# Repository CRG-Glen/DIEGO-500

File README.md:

# DIEGO PROJECT

Turn your A500 into an A2000 with this sidecar backplane
CHECKMATE VERSION NOT YET TESTED - DO NOT BUILD

## What's this?  

DIEGO is a Zorro 2 backplane expansion for use on your A500 either as a side car project or within your Checkmate case.  Diego gives you an A2000 compatible CO-PROCESSOR slot (side car version only) along with a full set of 5 ZORRO2 slots all made possible by the onboard Bluster IC.  Bluster is a remake of the classic A2000 Buster chip by LIV2 although it is a custom version for DIEGO to handle inverted clocks and provide some further functions.  

DIEGO has been tested extensively with various CPU and Zorro cards, a list of tested cards is provided below.  If you have anything to add to this list, please get in touch.  

DIEGO is also intended to power your A500 via the passthrough 4 pin connector adjacent to the main 24 pin ATX connector.  Please note that on the Checkmate version has power connected at the side car but also space for a passthrough.  The side car version currently does not have power connected at the side car.  For this version you must use the pass through to power your A500.  

## Ordering

There are currently 3 versions of DIEGO, a side car 5 slot version, a side car 3 slot version and a version for installation within a Checkmate case.  Please note that at present both the 3 slot and checkmate versions have not been tested so build at your own risk.  Checkmate version is currently in testing, I do not recommend building until it's confirmed working and ready.  

Gerber, BOM and CPL files are provided for each in the JLCPCB folder.  

All passives on each version are located on the bottom side (with exception of ferrite bead on checkmate version).  All logic and electrolytic caps are located on the top side.  

Each version of DIEGO is a 4 layer board.  HASL finish is fine for this project, inner layers can be left 0.5oz.  

All signals are routed on the top and bottom layers but there are some power traces on each internal layer along with solid grounds.  

Due to the amount of passives I recommend having your PCB manufacturer fit the bottom side, you then as builder complete the top side.  

While all components are available at JLC several top side parts are getting expensive!  

## Assembly

Assuming you got your boards made with the bottom side completed you may fit out the top side to suit yourself.  I recommend fitting and programming the CPLD first and finish all SMD work before doing the slots as they'll just get in the way!  

NOTE (side car version only): U11 is only required if you're using something in the COPROCESSOR slot that needs a 28mhz clock.  There doesn't seem to be that many (if any) cards that do require this so you may leave this off if you prefer. (this has not been tested as I don't have anything that needs this clock)

FURTHER NOTE: You MUST use LS and ALS logic as per the BOM.  DIEGO was originally built with HCT logic but this caused issues with several boards.  HCT will work if you prefer to use this but you might find some early SCSI cards don't work.  

For the 86pin slot to the A500 on the side car version you will need to bend the pins in to meet the pads on DIEGO.  

For programming the CPLD, the required JED file is available in the CPLD folder or you may get it from LIV2s GitHub.  I use a Raspberry PI to programme CPLDs as per LIV2s guide but use whatever method you're comfortable with.  Just remember if using a PI and if powering 3.3v from the PI, disconnect all other power supplies from DIEGO 500!

## Using your DIEGO

For the most part DIEGO is simply plug and play but there are a few things to keep in mind.
- Firstly there is a single jumper to configure to select which 7mhz clock to use.  If you're using a Rev3 or 5 A500 you must select CPLD clock.  If you're using a Rev6 A500 you can use either but if using A500 clock you need to close JP6 on the A500s motherboard.  If you are using an A500+ you can pick either.  The CPLD clock is derived from _CCK XNOR _CCQK within the CPLD.    
- There is one more pin header labelled CFGIN.  If you have any expansions in your A500 on the autoconfig chain you MUST connect said expansions config out to this config in.  If you don't you'll most likely get a yellow screen or just no zorro cards detected!
- Insert all cards as if this was a real A2000 i.e. the front of DIEGO is the front of an A2000.  Most modern Zorro expansions (especially half length cards) will have an arrow pointing to front or back.  Pay attention to this! If you plug something in wrong expect a dead card and possibly dead Amiga! 
- Zorro 2 cards will autoconfigure themselves just like they would in any Amiga.  To confirm this hold both mouse buttons on start up to access the early start-up menu and select "expansion board diagnostic" (only available to kickstart 2.04 and up)

Side car version only
-  If you're using a true A2000 CPU card in the COPROCESSOR slot (like the N2630) simply insert the card and Bluster will tristate the internal A500 CPU. (this is achieved by Bluster monitoring _BOSS and when asserted, Bluster asserts _BR to the internal CPU)  
- If you are using an A500 type accelerator in the COPROCESSOR slot such as TF536 or a PISTORM (including PISTORM 2000), you MUST open the A500 and remove the internal CPU.  Even if you manually assert _BOSS, the E clocks will clash and it won't work.  There is NO fix for this!  A2000 accelerators work as they monitor E and sync to it or generate it as necessary.  

Checkmate version only
- If you're using an accelerator in the A500s CPU socket you may need to connect its config out to the config in pin on DIEGO.  If you get a yellow screen or crash on boot this is the likely cause.  

## Testing and Results

With thanks to GADGETUK, SPARX, CATHERS and ANDI@HBR we've been able to test and confirm that most boards 
work fine in DIEGO.  The below table lists those boards tested and confirmed as working or not.

| Card Type | Name | Status |
|---|---|---|
| SCSI | Commodore A2090A | Working but very fussy (requires LS and ALS logic).  Only bluescsi V2 and only in raw mode. |
| SCSI | Commodore A2091 | Working |
| SCSI | GVP Series II HC+8 | Working |
| IDE |	Ripple IDE | Working |
| IDE |	AT-Bus clone | Working |
| IDE |	Buddha | Working |
| RAM |	Amigakit ZORRAM | Working |
| RAM |	Gottagofastram 2000 | Working |
| Sound | Prelude | Working |
| Sound | Toccata | Working |
| Sound | AD516 audio card | Working |
| RTG |	GBAPII | Working |
| RTG |	Merlin | Working |
| Networking |	Hydranet | Working |
| IO | BSC Multiface 3 | Working |
| IO | Thylacine USB (old longer model) | Working |
| Multi-feature | LAN-IDE-Clock | Working/Working/Not tested |
| CPU |	A2630 | Working |
| CPU |	N2630 | Working |
| CPU |	TF520 | Working |
| CPU |	TF536 | Working |
| CPU |	TK2 | Working |
| CPU |	Pistorm | Working |
| CPU |	Pistorm 2k | Working |
| Bridgeboard |	Commodore A2286 | Working |
| Bridgeboard |	Commodore A2086 | Working |

If you can add to this table please get in touch!

## Case

At present there is no full case but there is a base that will hold either the 3 or 5 slot version of Diego level with the side car slot of your A500.  I'm not great at designing these things so if you want to help please get in touch.  STL files are in the BASE folder.  

With thanks to Maikiro on Discord we now had a proper base for the 5 slot version.  He has kindly created 3 version of this to suit positioning of your ATX power connector.  STLs for these are provided in the BASE/Maikiro folder.

## FAQ

Several people have asked about adding ISA slots, a video slot or making this remote with a ribbon cable to the A500.  

ISA slots - DIEGO side car has been designed so that you could in theory add ISA slots on a separate board, the Zorro slots 
in relation to the edge of the PCB are positioned to allow this.  I haven't designed an ISA slot extension as I don't have a bridge board to test it with.  
The Checkmate version could be redesigned to incorporate ISA slots although you will loose 2 of the half length zorro slots.  For this release it was thought more useful to include 5 zorro slots. 

Video slot - There are no plans to add a video slot.  Very few of the required signals are on the A500s side car so it would need a multicore ribbon from DENISE.  

Ribbon Cable for remote use - If you want to try a ribbon cable to have DIEGO remote from your 500 you can simply solder one onto the edge connector but I don't expect this to work without further buffering! (like in the bodega bay).

A1000 version - This is coming along with a rework of the entire project to sit vertical beside your 500.  It'll take a while to figure out so please bear with me.  

## License

This project represents countless hours of work by not just me but LIV2 and everyone involved in testing.  It is however released under a CERN Open Hardware Licence v2 for the community to enjoy.  

While I cannot put any direct stipulations into this I would ask that it should only be built and sold at cost plus time.  

If you plan on forking or using this as the basis for any other works you must comply with the following as per the terms of the license attributed to this project.
1. All attributions and credits as presented within this github and on the DIEGO 500 PCB must be maintained and carried through.
2. Any derivative of this project must be also be released open source.

If you are doing a build of these please consider a £1 donation per board to my kofi - https://ko-fi.com/crg_glen.  I'm at least £500 into this project so any support to recoup this is appreicated.  

## Credits

Based on A2000 rev6 schematics by Dave Haynie and EATX2000 by Jasonsbeer

PCB by CRG(Glen)

Bluster by LIV2

Artwork by Brick Studios

Testing by GadgetUK, Sparx, Cathers and Andi@HBR

Thanks to Mikerochip for inspiration for the PSU switch, Neil from Retro4U for loaning his GVP for testing and Kazanoz for helping with the BOM

Special thanks to GadgetUK for hosting the test room on his discord and LIV2 for his work modifying Bluster

Extra Special thanks to Rob Cranley and Steve Jones for their help on the Checkmate version

Why is it called Diego?  Well... this project started solely as a Zorro 2 expansion and to implement that I first had
to understand how the Zorro bus worked.  You might say I had to unmask Zorro.  The character of Zorro unmasked is called Don Diego so Diego 500 or Diego Checkmate.

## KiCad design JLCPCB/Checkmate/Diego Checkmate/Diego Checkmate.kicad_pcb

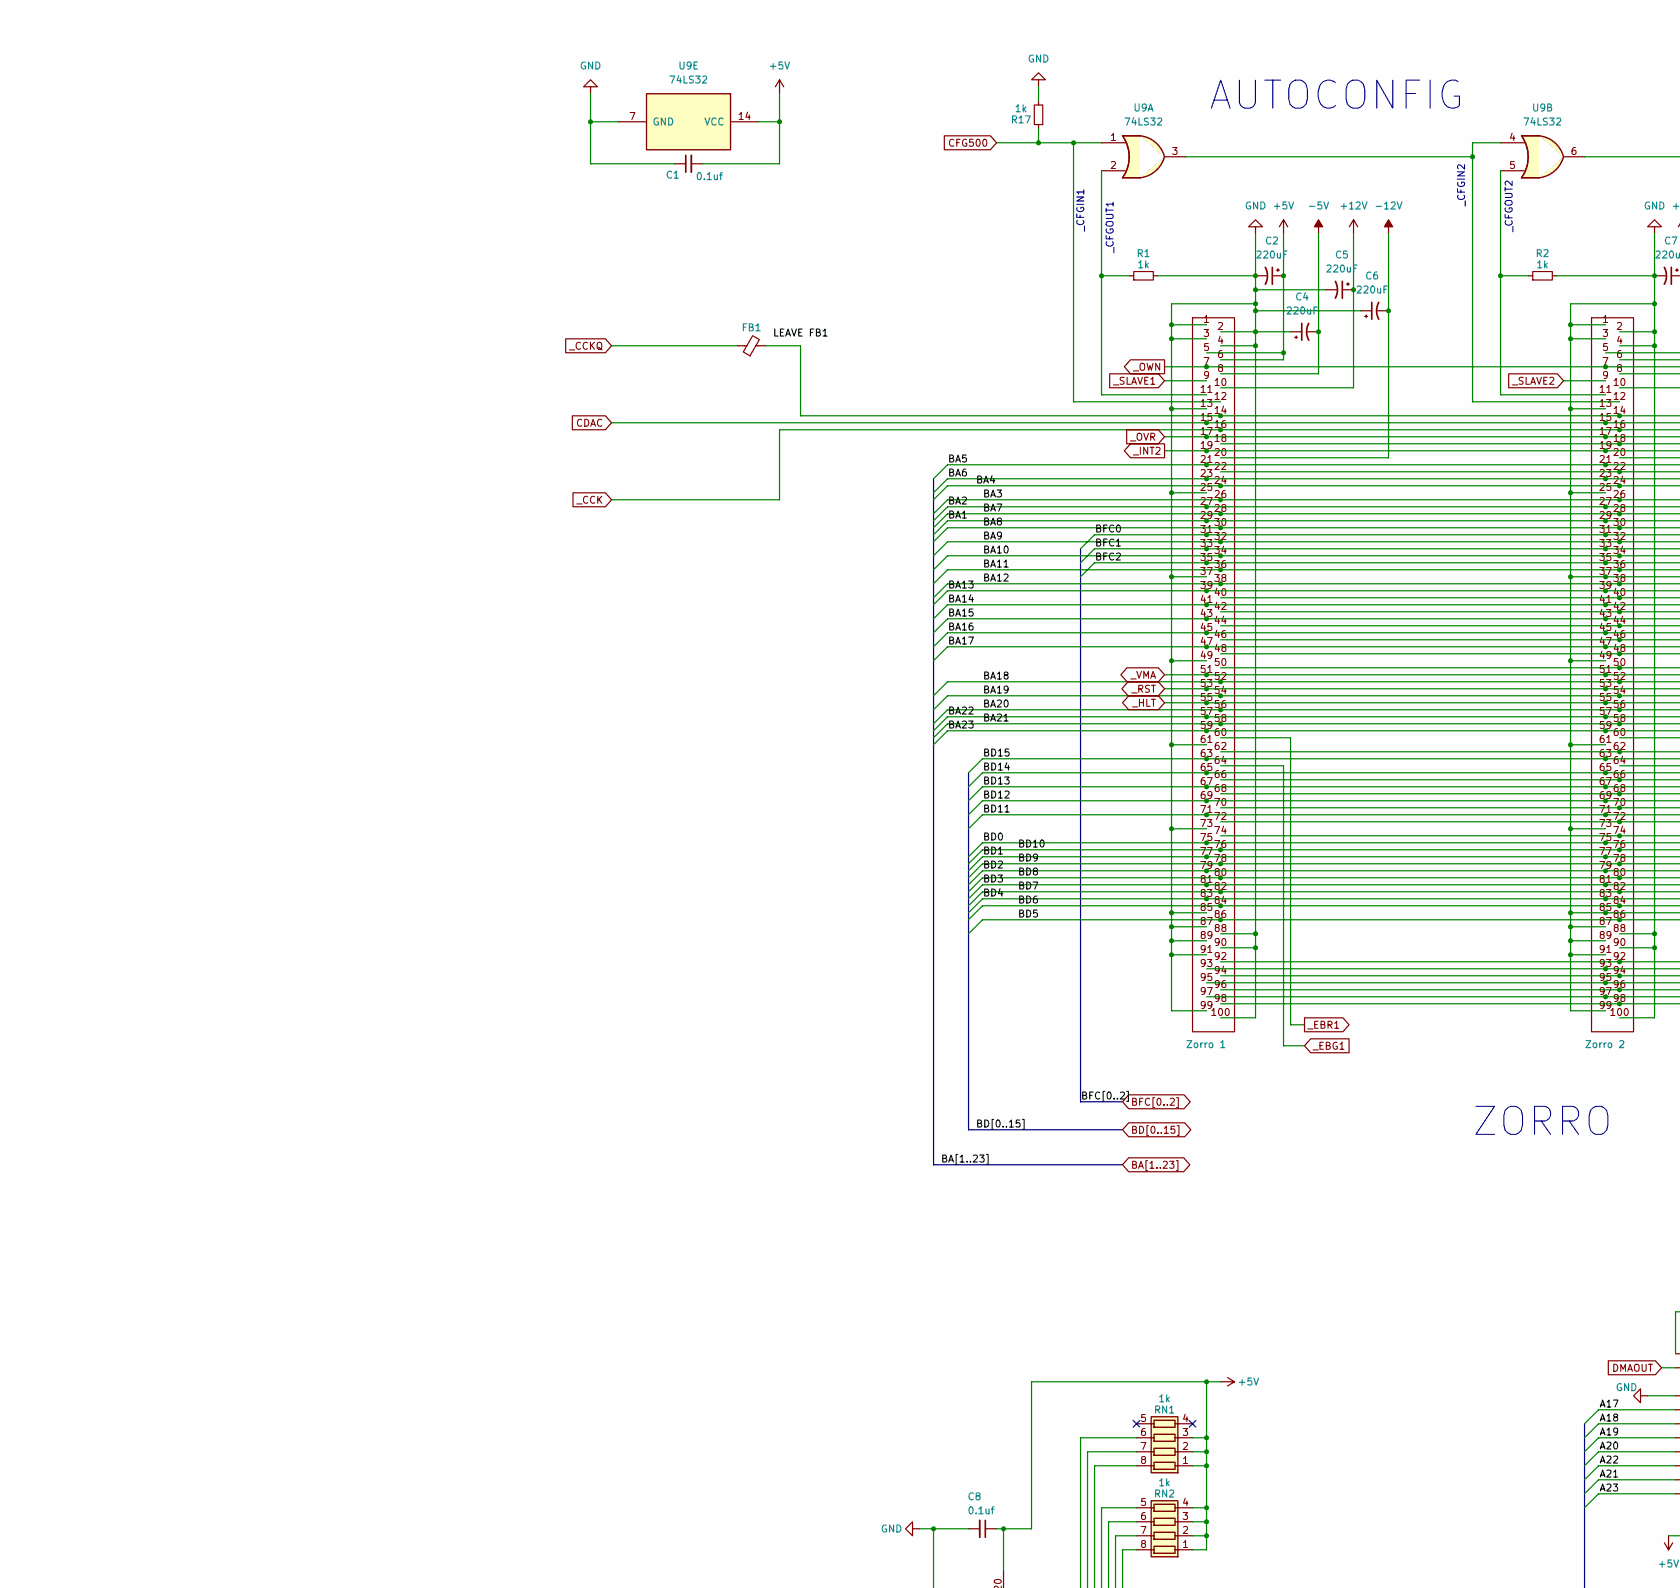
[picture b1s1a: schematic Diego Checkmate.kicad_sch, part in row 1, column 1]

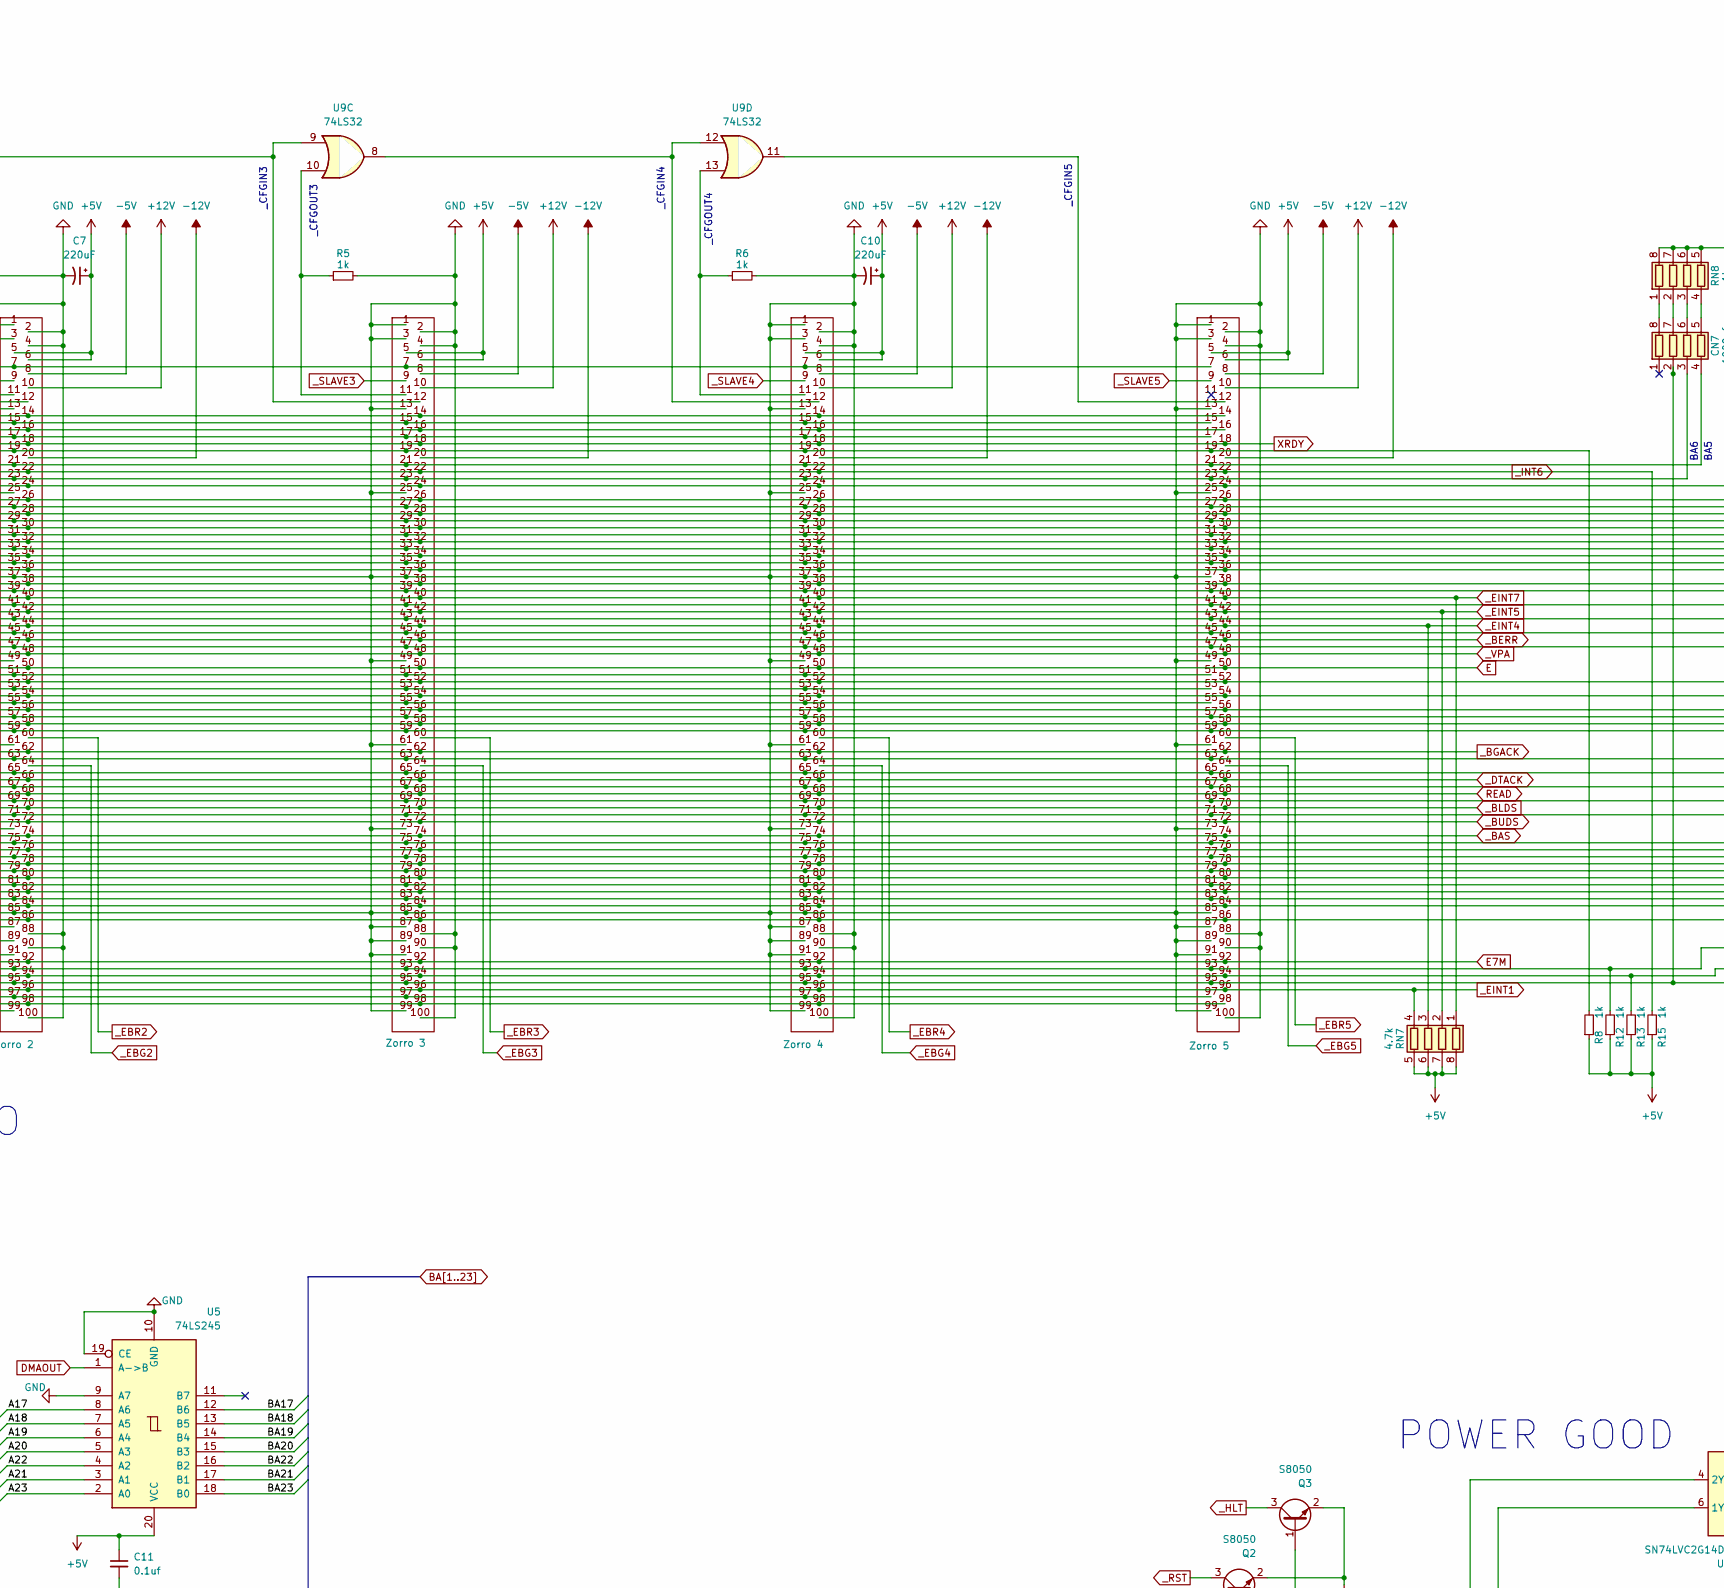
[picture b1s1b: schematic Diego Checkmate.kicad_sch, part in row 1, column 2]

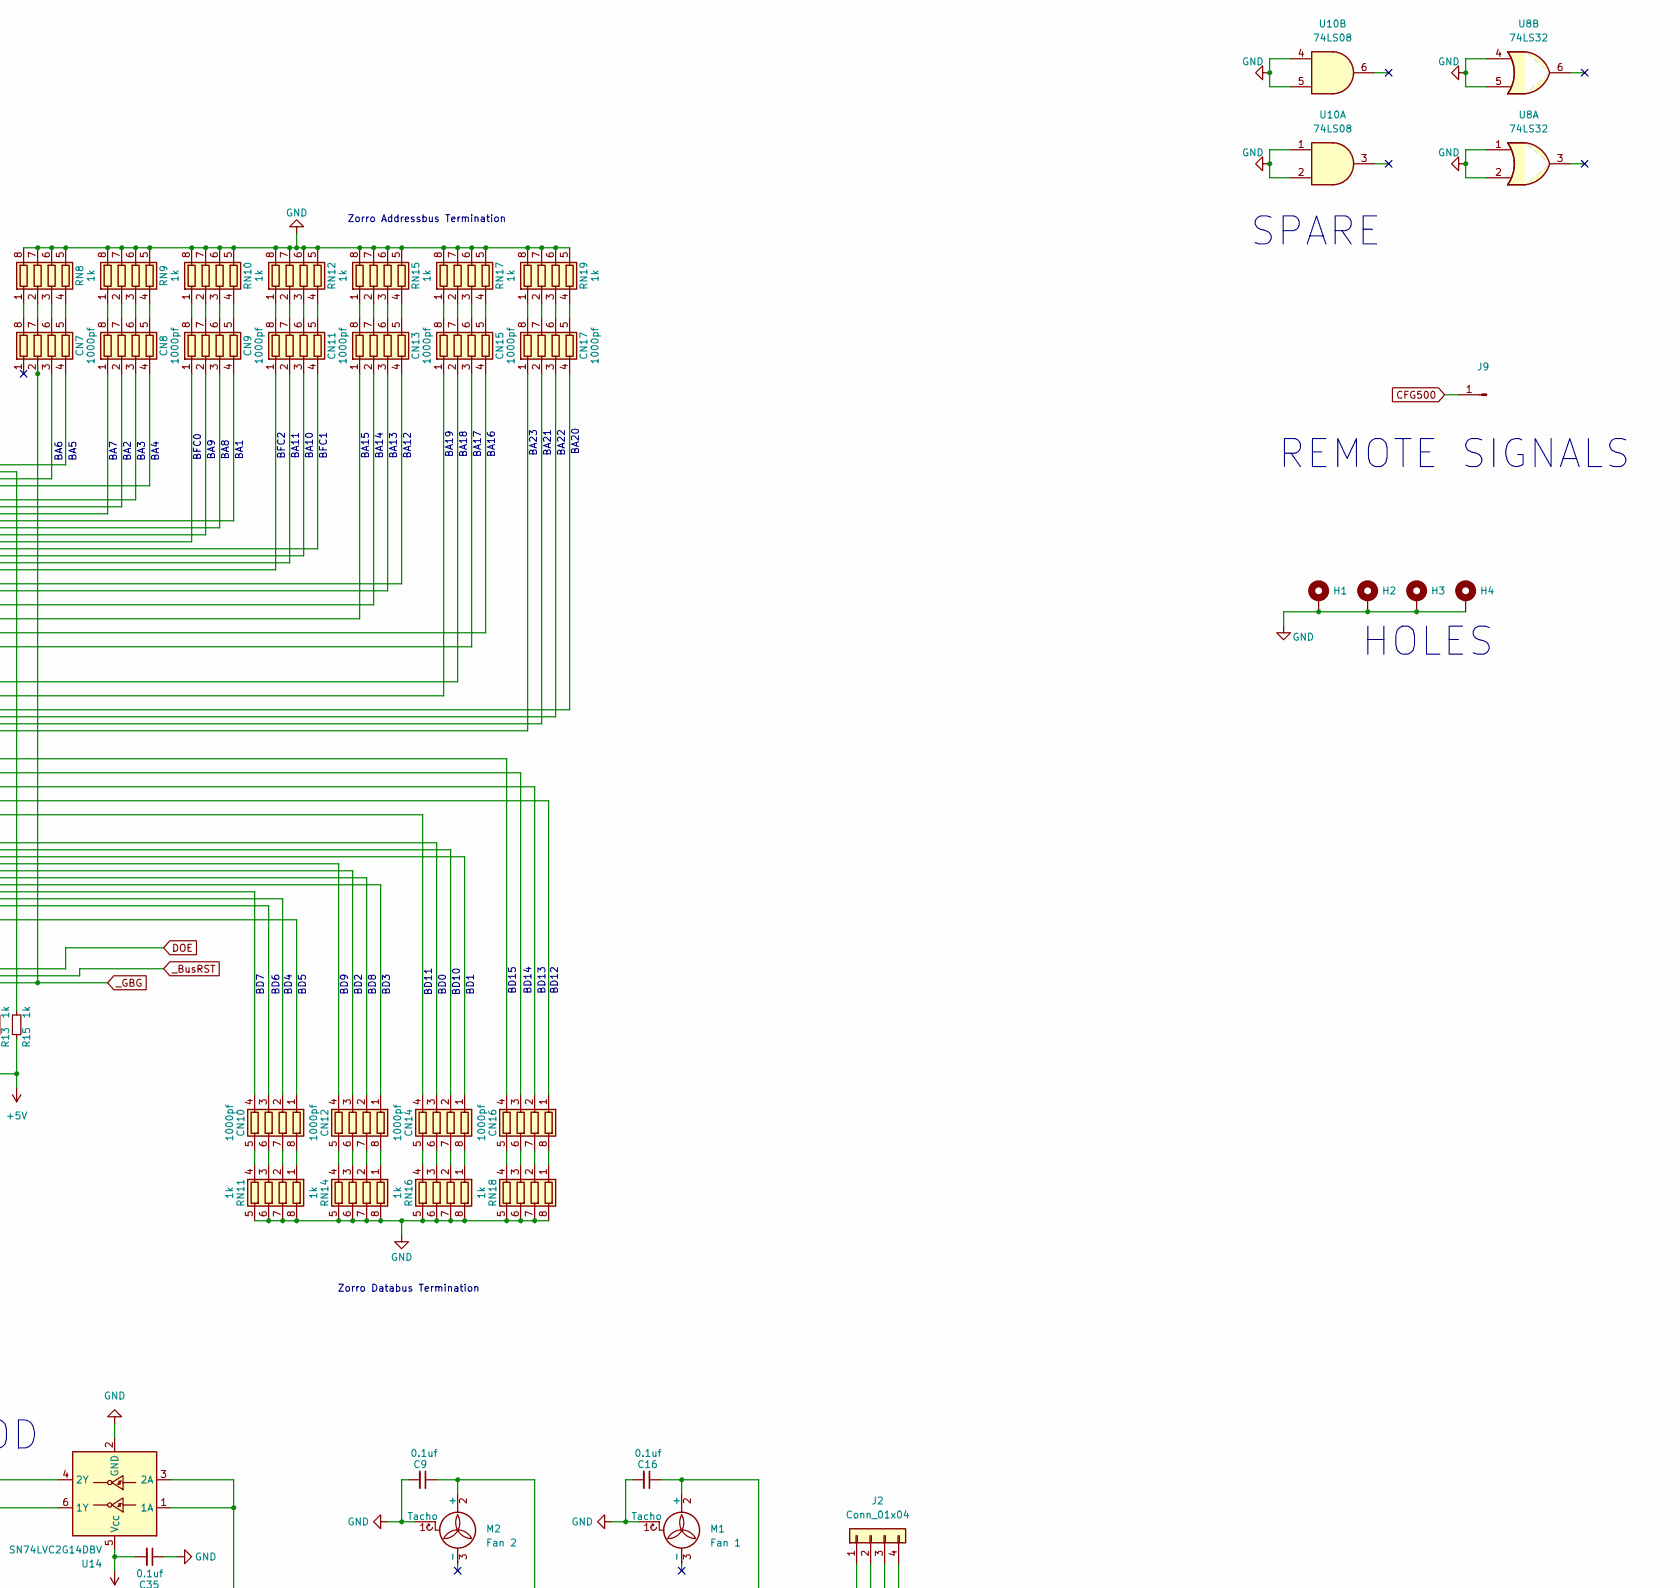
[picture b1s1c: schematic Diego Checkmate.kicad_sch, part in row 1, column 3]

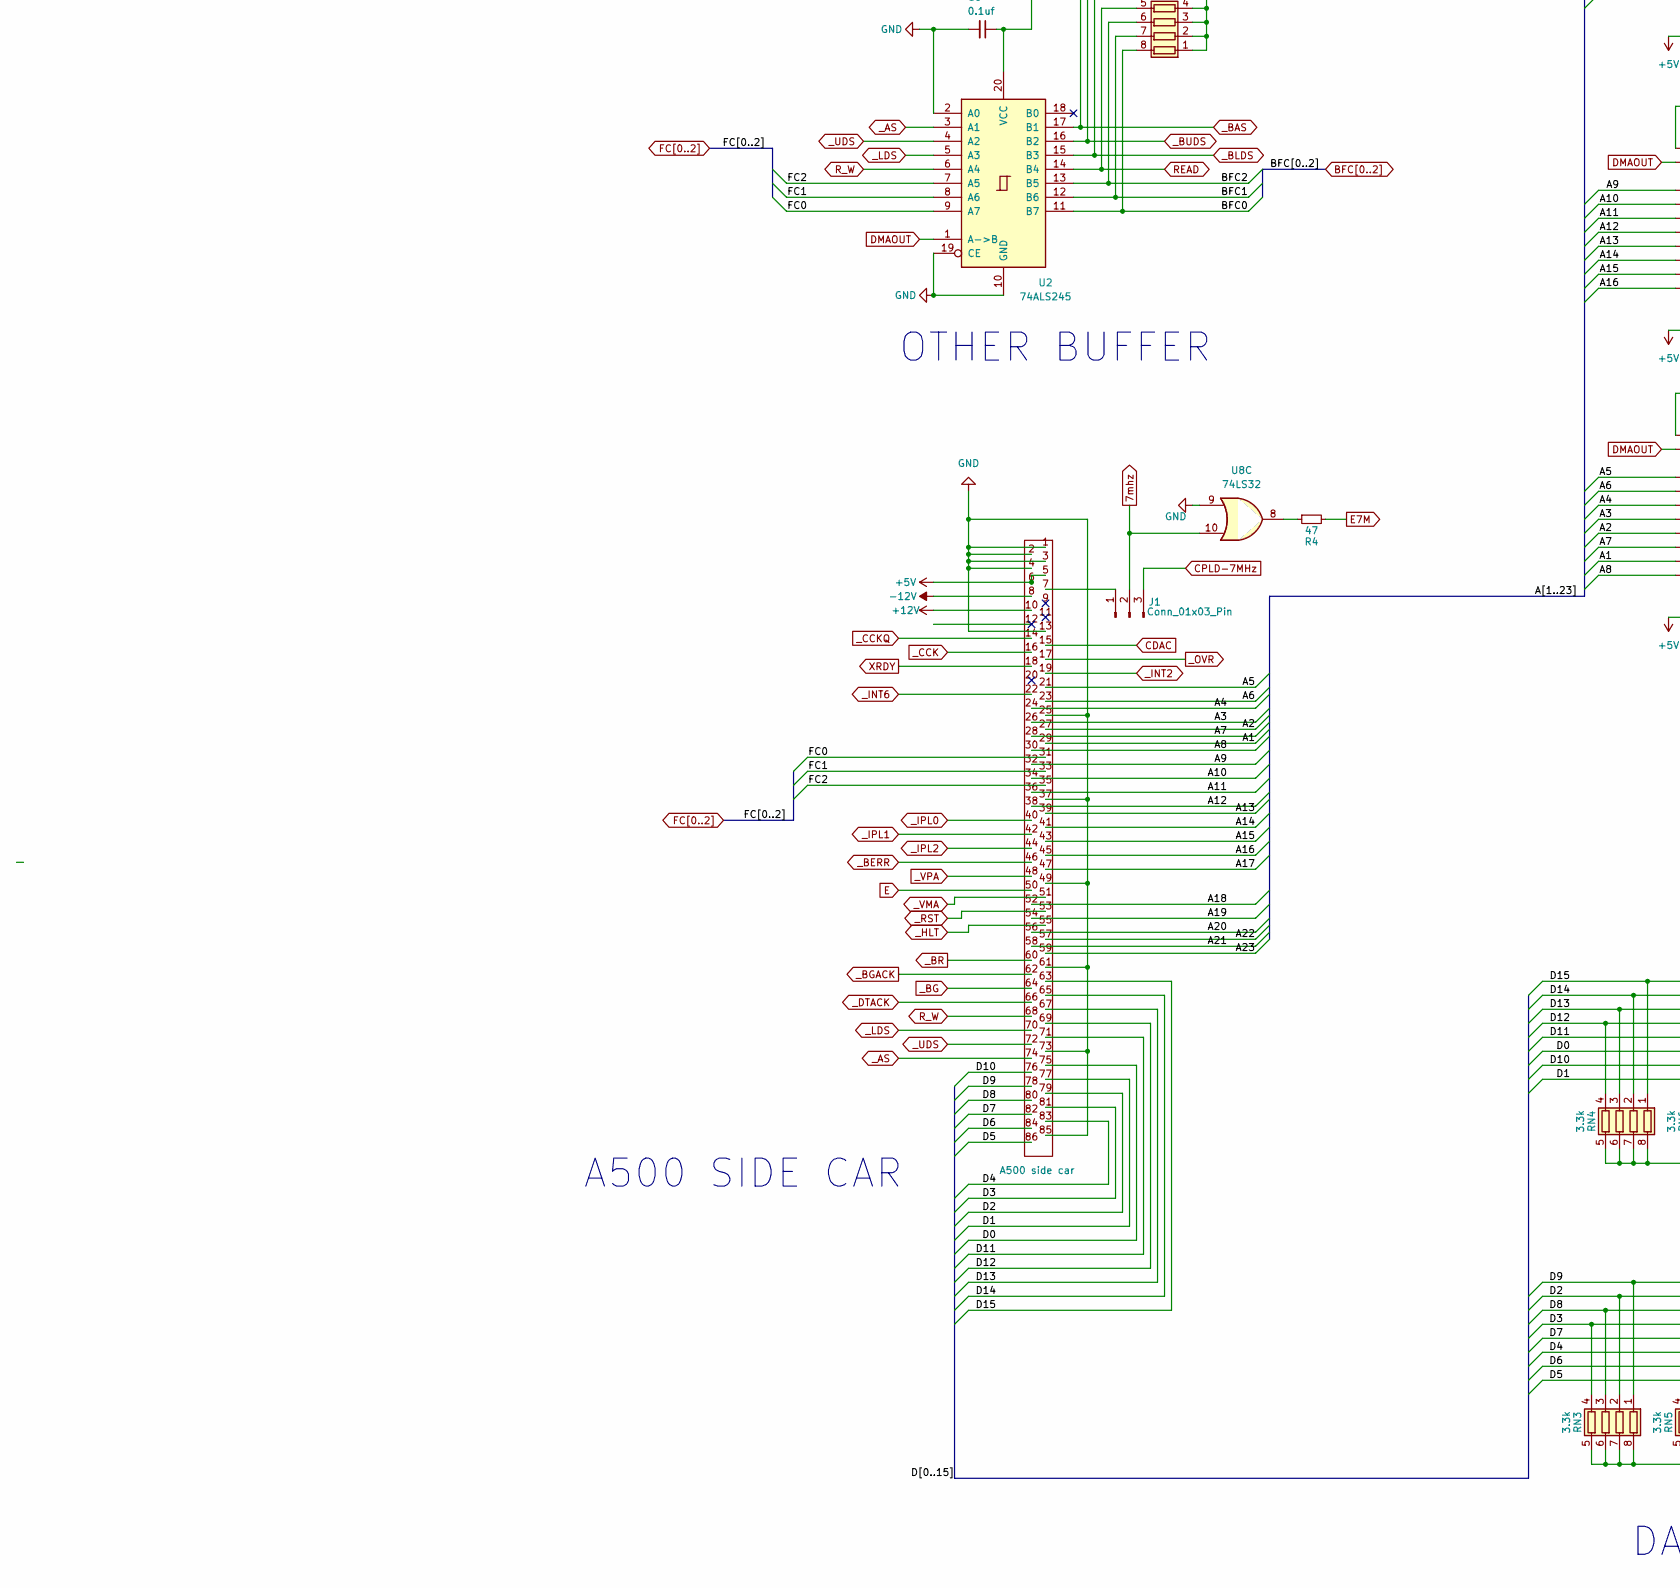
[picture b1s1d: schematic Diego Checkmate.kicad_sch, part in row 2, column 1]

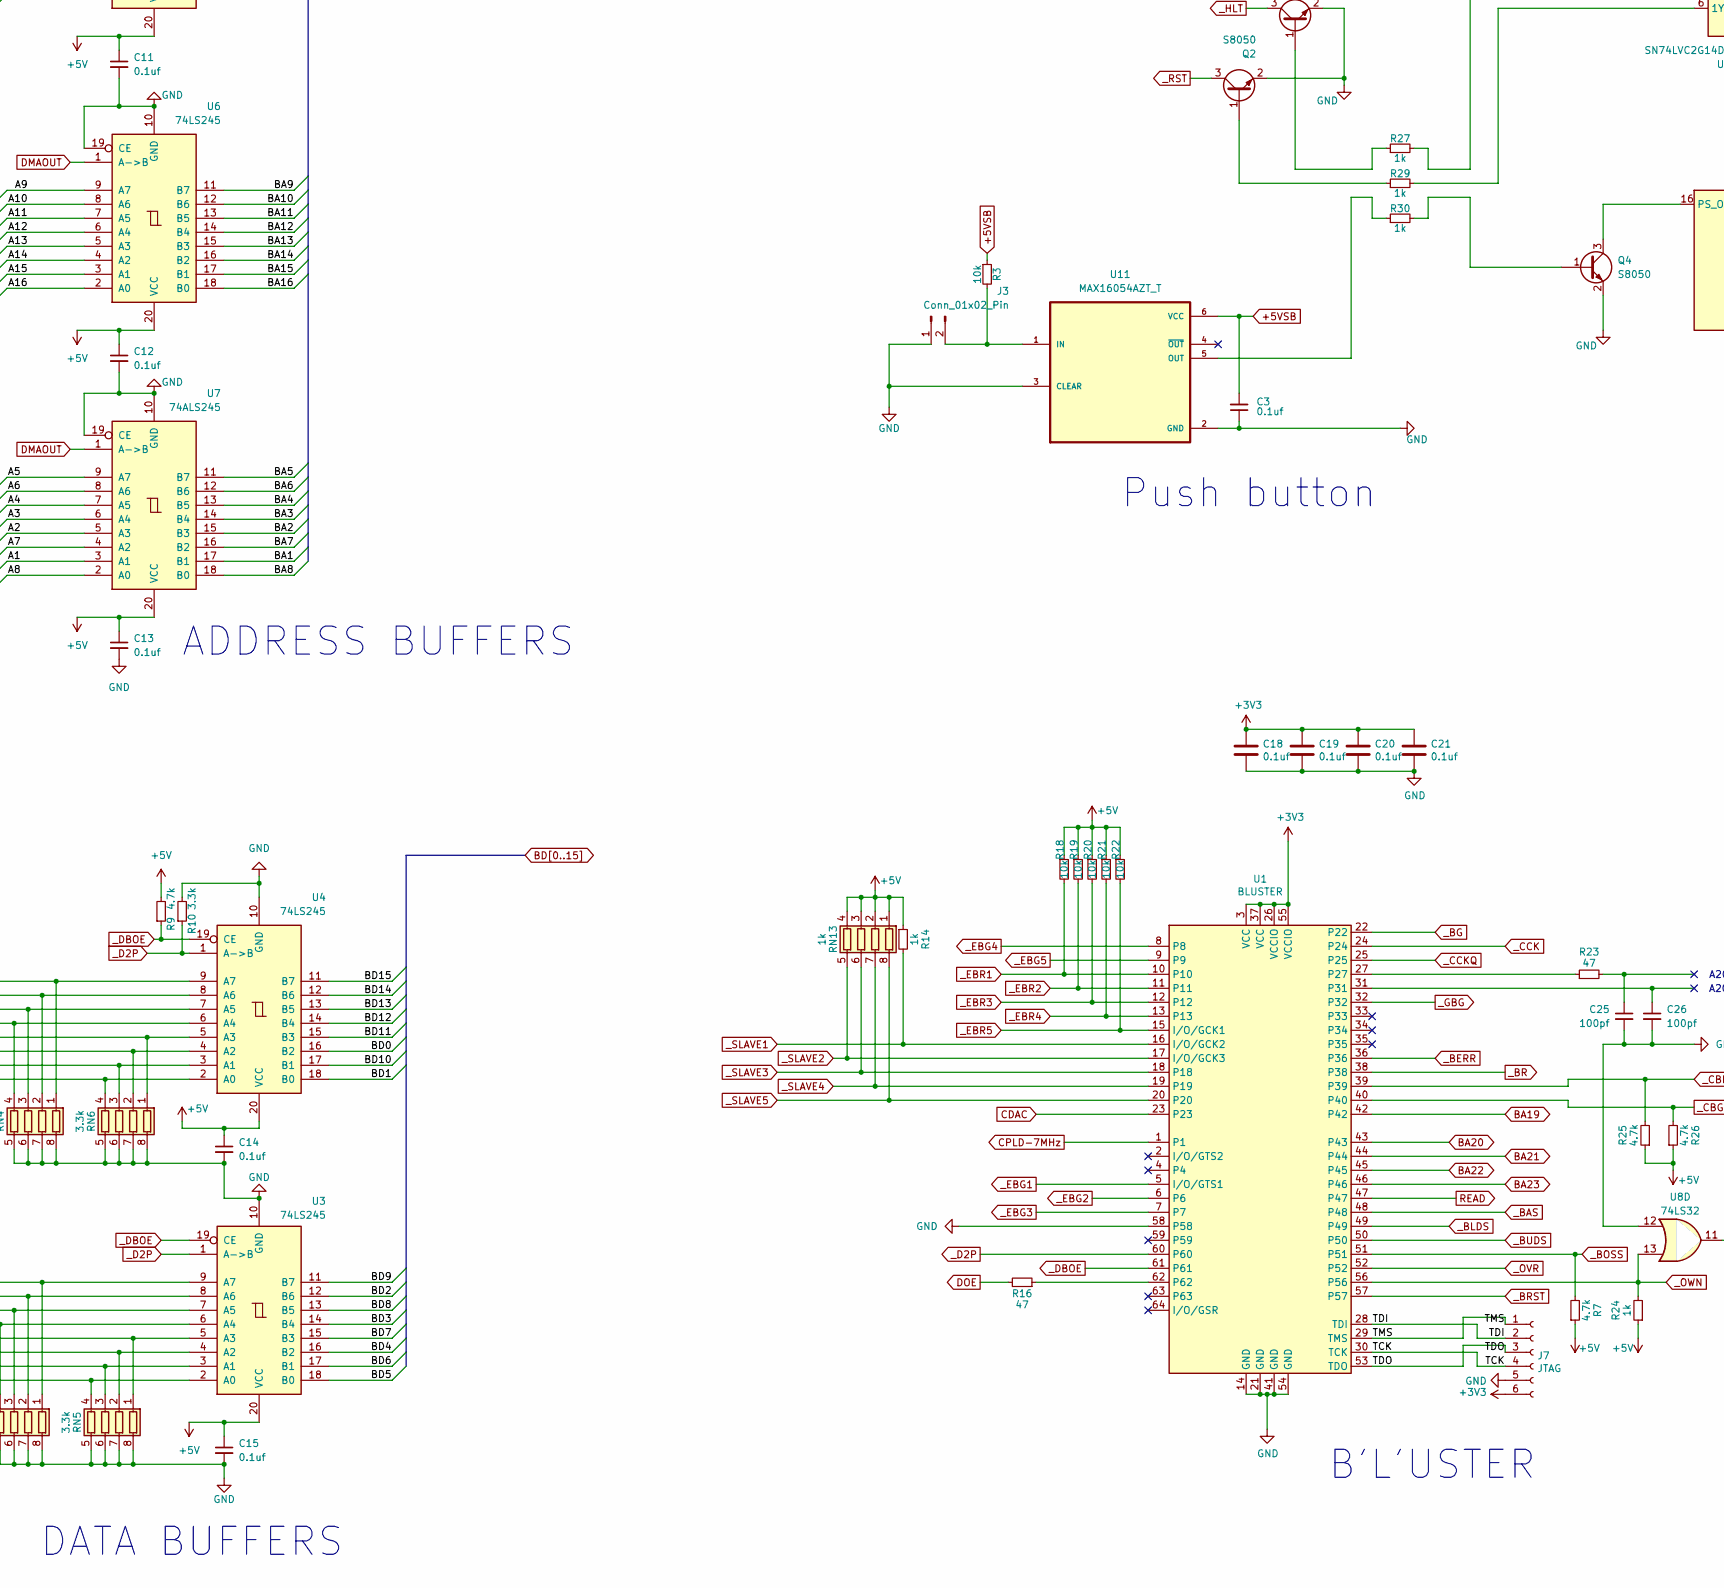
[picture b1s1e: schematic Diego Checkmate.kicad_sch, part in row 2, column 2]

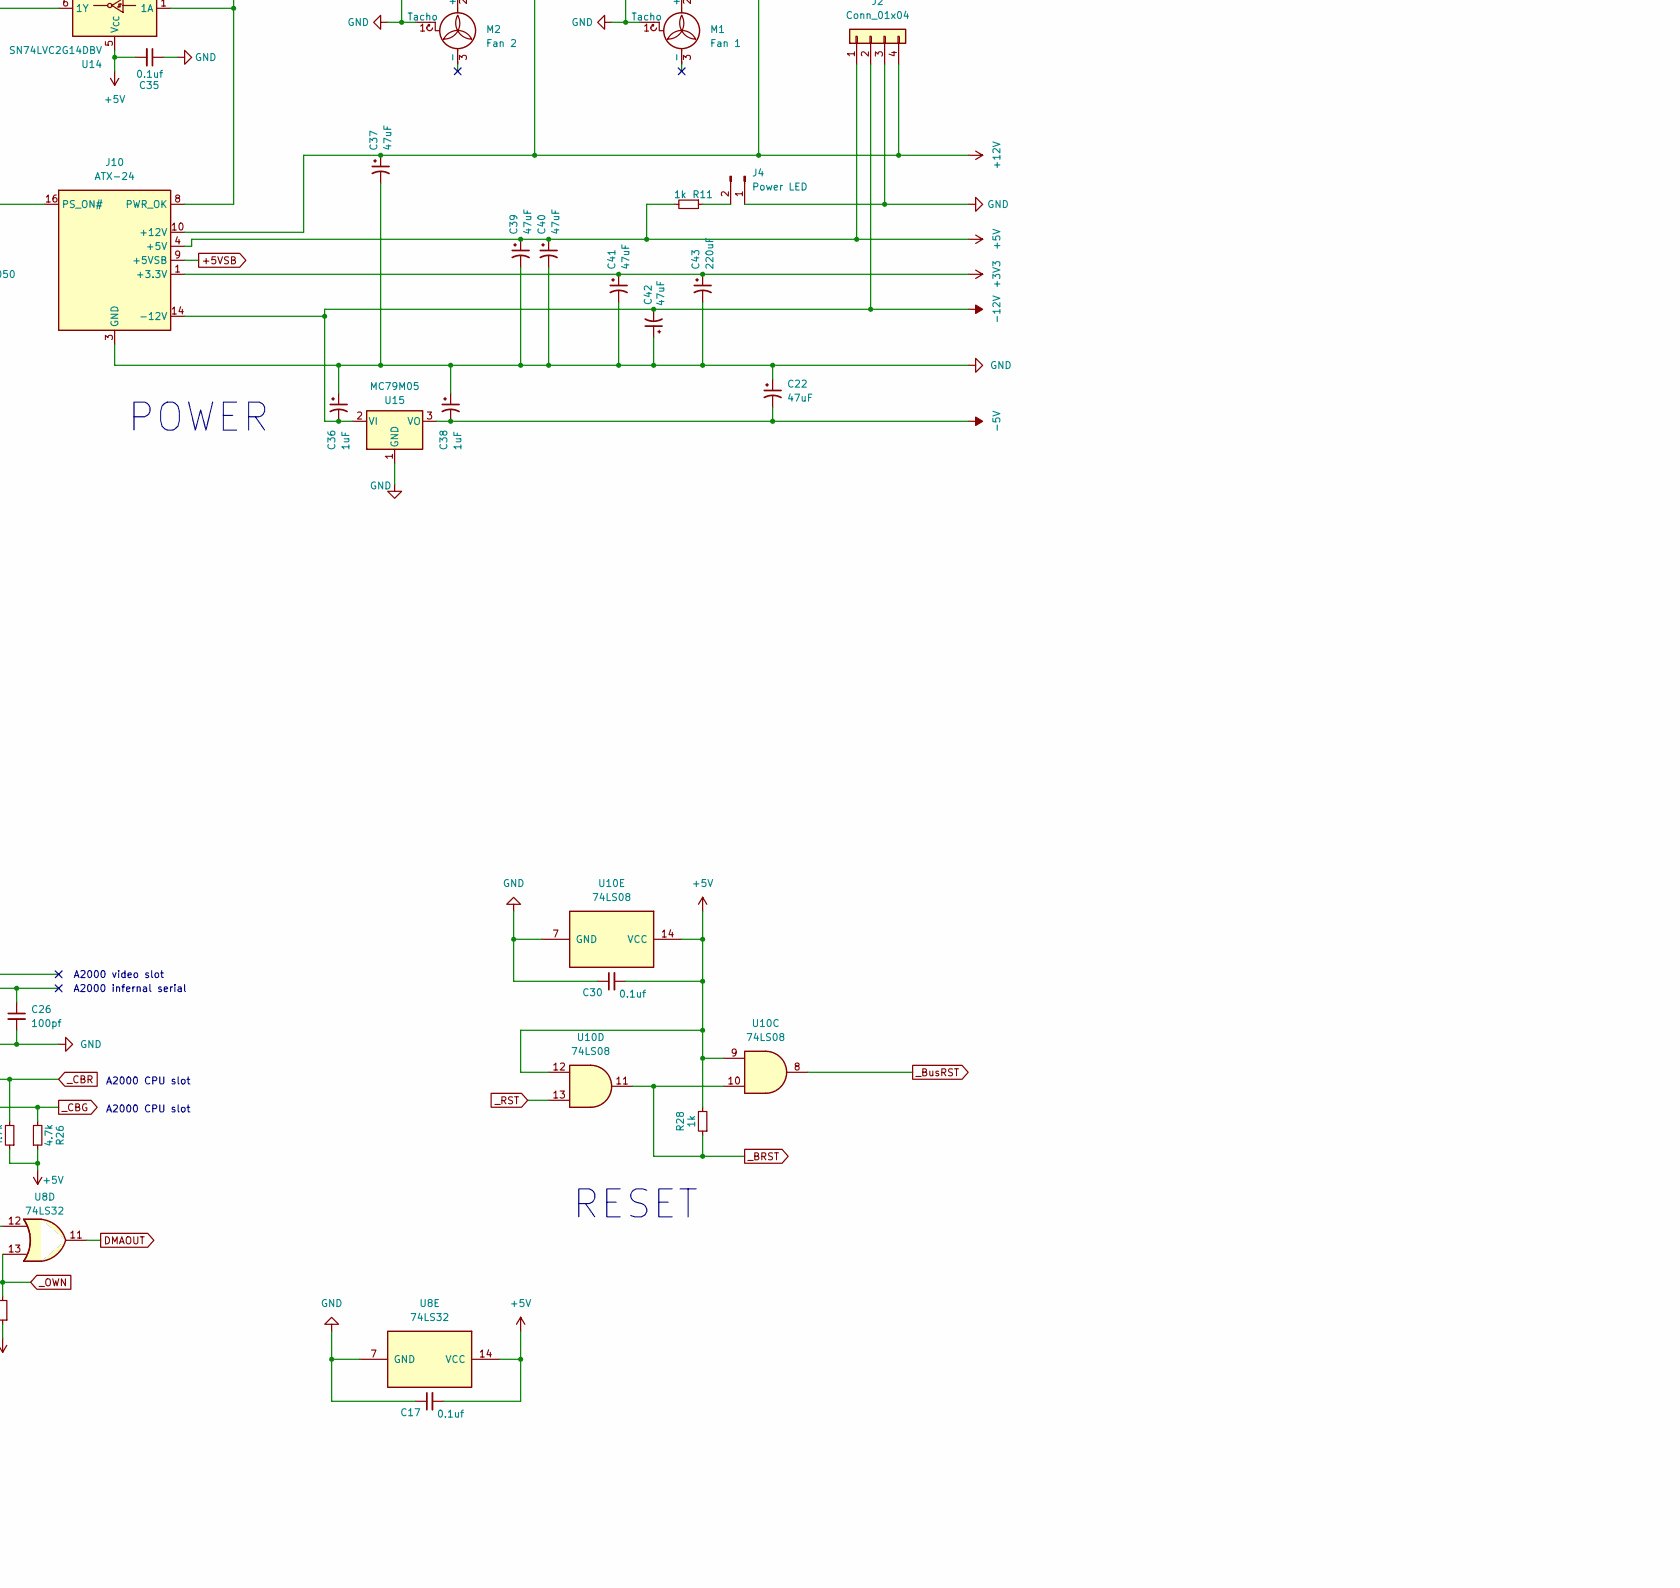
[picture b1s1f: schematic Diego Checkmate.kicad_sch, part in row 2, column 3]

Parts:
C1, C3, C8, C9, C11, C12, C13, C14, C15, C16, C17, C30, C35: 0.1uf; C_0805_2012Metric; LCSC C49678
C2, C4, C5, C6, C7, C10, C43: 220uF; CP_Elec_6.3x7.7; LCSC C278407
C18, C19, C20, C21: 0.1uf; C_0805_2012Metric_Pad1.18x1.45mm_HandSolder; LCSC C49678
C22, C37, C39, C40, C41, C42: 47uF; CP_Elec_6.3x7.7; LCSC C336249
C25, C26: 100pf; C_0805_2012Metric; LCSC C1790
C36, C38: 1uF; CP_Elec_4x5.4; LCSC C3348
CN1: A500 side car; Samtec_HLE-150-02-xx-DV-TE_2x43_P2.54mm_Horizontal; LCSC C5173317
CN2: Zorro 1; Samtec_HLE-150-02-xx-DV-TE_2x50_P2.54mm_Horizontal; LCSC C5173320
CN3: Zorro 2; Samtec_HLE-150-02-xx-DV-TE_2x50_P2.54mm_Horizontal; LCSC C5173320
CN4: Zorro 3; Samtec_HLE-150-02-xx-DV-TE_2x50_P2.54mm_Horizontal; LCSC C5173320
CN5: Zorro 4; Samtec_HLE-150-02-xx-DV-TE_2x50_P2.54mm_Horizontal; LCSC C5173320
CN6: Zorro 5; Samtec_HLE-150-02-xx-DV-TE_2x50_P2.54mm_Horizontal; LCSC C5173320
CN7, CN8, CN9, CN10, CN11, CN12, CN13, CN14, CN15, CN16, CN17: 1000pf; R_Array_Convex_4x0603; LCSC C541606
FB1: FerriteBead_Small; D_0805_2012Metric; LCSC C1015
H1, H2, H3, H4: MountingHole_Pad; MountingHole_4.3mm_M4_DIN965_Pad_TopBottom
J1: Conn_01x03_Pin; PinHeader_1x03_P2.54mm_Vertical
J2: Conn_01x04; Molex_KK-396_A-41791-0004_1x04_P3.96mm_Vertical
J3: Conn_01x02_Pin; PinHeader_1x02_P2.54mm_Vertical
J4: Power LED; PinHeader_1x02_P2.54mm_Vertical
J7: JTAG; PinHeader_1x06_P2.54mm_Vertical
J9: Conn_01x01_Pin; PinHeader_1x01_P2.54mm_Vertical
J10: ATX-24; Molex_Mini-Fit_Jr_5566-24A_2x12_P4.20mm_Vertical
M1: Fan 1; FanPinHeader_1x03_P2.54mm_Vertical
M2: Fan 2; FanPinHeader_1x03_P2.54mm_Vertical
Q2, Q3, Q4: S8050; SOT-23; LCSC C2146
R1, R2, R5, R6, R8, R11, R12, R13, R14, R15, R17, R24, R27, R28, R29, R30: 1k; R_0805_2012Metric; LCSC C17513
R3, R18, R19, R20, R21, R22: 10k; R_0805_2012Metric; LCSC C17414
R4, R16, R23: 47; R_0805_2012Metric; LCSC C17714
R7, R9, R25, R26: 4.7k; R_0805_2012Metric; LCSC C17673
R10: 3.3k; R_0805_2012Metric; LCSC C26010
RN1, RN2, RN8, RN9, RN10, RN11, RN12, RN13, RN14, RN15, RN16, RN17, RN18, RN19: 1k; R_Array_Convex_4x0603; LCSC C20197
RN3, RN4, RN5, RN6: 3.3k; R_Array_Convex_4x0603; LCSC C425215
RN7: 4.7k; R_Array_Convex_4x0603; LCSC C66697
U1: BLUSTER; TQFP-64_10x10mm_P0.5mm; LCSC C90569
U2, U7: 74ALS245; SO-20_5.3x12.6mm_P1.27mm; LCSC C2675885
U3, U4, U5, U6: 74LS245; SO-20_5.3x12.6mm_P1.27mm; LCSC C7753
U8, U9: 74LS32; SO-14_3.9x8.65mm_P1.27mm; LCSC C116812
U10: 74LS08; SO-14_3.9x8.65mm_P1.27mm; LCSC C6802
U11: MAX16054AZT_T; SOT-23-6; LCSC C79401
U14: SN74LVC2G14DBV; SOT-23-6; LCSC C12401
U15: MC79M05; TO-252-2; LCSC C126401

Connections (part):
7mhz: J1.2, U8.10
+3V3: C18.1, C19.1, C20.1, C21.1, C41.1, C43.1, J7.6, J10.1 (+3.3V), J10.2 (+3.3V), J10.12 (+3.3V), J10.13 (+3.3V), U1.3 (VCC), U1.26 (VCCIO), U1.37 (VCC), U1.55 (VCCIO)
+5V: C1.2, C2.1, C7.1, C8.1, C10.1, C11.1, C12.1, C13.1, C14.1, C15.1, C17.2, C30.2, C35.2, C39.1, C40.1, CN1.5, CN1.6, CN2.5, CN2.6, CN3.5, CN3.6, CN4.5, CN4.6, CN5.5, CN5.6, CN6.5, CN6.6, J2.1, J10.4 (+5V), J10.6 (+5V), J10.21 (+5V), J10.22 (+5V), J10.23 (+5V), R7.1, R8.1, R9.2, R11.2, R12.1, R13.1, R14.1, R15.1, R18.1, R19.1, R20.1, R21.1, R22.1, R24.1, R25.1, R26.1, R28.2, RN1.1 (R1.1), RN1.2 (R2.1), RN1.3 (R3.1), RN2.1 (R1.1), RN2.2 (R2.1), RN2.3 (R3.1), RN2.4 (R4.1), RN7.5 (R4.2), RN7.6 (R3.2), RN7.7 (R2.2), RN7.8 (R1.2), RN13.1 (R1.1), RN13.2 (R2.1), RN13.3 (R3.1), RN13.4 (R4.1), U2.20 (VCC), U3.20 (VCC), U4.20 (VCC), U5.20 (VCC), U6.20 (VCC), U7.20 (VCC), U8.14 (VCC), U9.14 (VCC), U10.9, U10.12, U10.14 (VCC), U14.5 (V_{CC})
+5VSB: C3.2, J10.9 (+5VSB), R3.1, U11.6 (VCC)
+12V: C5.1, C9.1, C16.1, C37.1, CN1.10, CN2.10, CN3.10, CN4.10, CN5.10, CN6.10, J2.4, J10.10 (+12V), J10.11 (+12V), M1.2 (+), M2.2 (+)
-5V: C4.2, C22.2, C38.2, CN2.8, CN3.8, CN4.8, CN5.8, CN6.8, U15.3 (VO)
-12V: C6.2, C36.2, C42.2, CN1.8, CN2.20, CN3.20, CN4.20, CN5.20, CN6.20, J2.2, J10.14 (-12V), U15.2 (VI)
/A1: CN1.29, U7.3 (A1)
/A2: CN1.27, U7.5 (A3)
/A3: CN1.26, U7.6 (A4)
/A4: CN1.24, U7.7 (A5)
/A5: CN1.21, U7.9 (A7)
/A6: CN1.23, U7.8 (A6)
/A7: CN1.28, U7.4 (A2)
/A8: CN1.30, U7.2 (A0)
/A9: CN1.32, U6.9 (A7)
/A10: CN1.34, U6.8 (A6)
/A11: CN1.36, U6.7 (A5)
/A12: CN1.38, U6.6 (A4)
/A13: CN1.39, U6.5 (A3)
/A14: CN1.41, U6.4 (A2)
/A15: CN1.43, U6.3 (A1)
/A16: CN1.45, U6.2 (A0)
/A17: CN1.47, U5.8 (A6)
/A18: CN1.52, U5.7 (A5)
/A19: CN1.54, U5.6 (A4)
/A20: CN1.56, U5.5 (A3)
/A21: CN1.58, U5.3 (A1)
/A22: CN1.57, U5.4 (A2)
/A23: CN1.59, U5.2 (A0)
/D0: CN1.75, RN6.2 (R2.1), U4.4 (A2)
/D1: CN1.77, RN6.4 (R4.1), U4.2 (A0)
/D2: CN1.79, RN3.2 (R2.1), U3.8 (A6)
/D3: CN1.81, RN3.4 (R4.1), U3.6 (A4)
/D4: CN1.83, RN5.2 (R2.1), U3.4 (A2)
/D5: CN1.86, RN5.4 (R4.1), U3.2 (A0)
/D6: CN1.84, RN5.3 (R3.1), U3.3 (A1)
/D7: CN1.82, RN5.1 (R1.1), U3.5 (A3)
/D8: CN1.80, RN3.3 (R3.1), U3.7 (A5)
/D9: CN1.78, RN3.1 (R1.1), U3.9 (A7)
/D10: CN1.76, RN6.3 (R3.1), U4.3 (A1)
/D11: CN1.71, RN6.1 (R1.1), U4.5 (A3)
/D12: CN1.69, RN4.4 (R4.1), U4.6 (A4)
/D13: CN1.67, RN4.3 (R3.1), U4.7 (A5)
/D14: CN1.65, RN4.2 (R2.1), U4.8 (A6)
/D15: CN1.63, RN4.1 (R1.1), U4.9 (A7)
/TCK: J7.4, U1.30 (TCK)
/TDI: J7.2, U1.28 (TDI)
/TDO: J7.3, U1.53 (TDO)
/TMS: J7.1, U1.29 (TMS)
BA1: CN2.29, CN3.29, CN4.29, CN5.29, CN6.29, CN9.4 (R4.1), U7.17 (B1)
BA2: CN2.27, CN3.27, CN4.27, CN5.27, CN6.27, CN8.2 (R2.1), U7.15 (B3)
BA3: CN2.26, CN3.26, CN4.26, CN5.26, CN6.26, CN8.3 (R3.1), U7.14 (B4)
BA4: CN2.24, CN3.24, CN4.24, CN5.24, CN6.24, CN8.4 (R4.1), U7.13 (B5)
BA5: CN2.21, CN3.21, CN4.21, CN5.21, CN6.21, CN7.4 (R4.1), U7.11 (B7)
BA6: CN2.23, CN3.23, CN4.23, CN5.23, CN6.23, CN7.3 (R3.1), U7.12 (B6)
BA7: CN2.28, CN3.28, CN4.28, CN5.28, CN6.28, CN8.1 (R1.1), U7.16 (B2)
BA8: CN2.30, CN3.30, CN4.30, CN5.30, CN6.30, CN9.3 (R3.1), U7.18 (B0)
BA9: CN2.32, CN3.32, CN4.32, CN5.32, CN6.32, CN9.1 (R1.1), U6.11 (B7)
BA10: CN2.34, CN3.34, CN4.34, CN5.34, CN6.34, CN11.3 (R3.1), U6.12 (B6)
BA11: CN2.36, CN3.36, CN4.36, CN5.36, CN6.36, CN11.1 (R1.1), U6.13 (B5)
BA12: CN2.38, CN3.38, CN4.38, CN5.38, CN6.38, CN13.4 (R4.1), U6.14 (B4)
BA13: CN2.39, CN3.39, CN4.39, CN5.39, CN6.39, CN13.3 (R3.1), U6.15 (B3)
BA14: CN2.41, CN3.41, CN4.41, CN5.41, CN6.41, CN13.2 (R2.1), U6.16 (B2)
BA15: CN2.43, CN3.43, CN4.43, CN5.43, CN6.43, CN13.1 (R1.1), U6.17 (B1)
BA16: CN2.45, CN3.45, CN4.45, CN5.45, CN6.45, CN15.4 (R4.1), U6.18 (B0)
BA17: CN2.47, CN3.47, CN4.47, CN5.47, CN6.47, CN15.3 (R3.1), U5.12 (B6)
BA18: CN2.52, CN3.52, CN4.52, CN5.52, CN6.52, CN15.2 (R2.1), U5.13 (B5)
BA19: CN2.54, CN3.54, CN4.54, CN5.54, CN6.54, CN15.1 (R1.1), U1.42, U5.14 (B4)
BA20: CN2.56, CN3.56, CN4.56, CN5.56, CN6.56, CN17.4 (R4.1), U1.43, U5.15 (B3)
BA21: CN2.58, CN3.58, CN4.58, CN5.58, CN6.58, CN17.2 (R2.1), U1.44, U5.17 (B1)
BA22: CN2.57, CN3.57, CN4.57, CN5.57, CN6.57, CN17.3 (R3.1), U1.45, U5.16 (B2)
BA23: CN2.59, CN3.59, CN4.59, CN5.59, CN6.59, CN17.1 (R1.1), U1.46, U5.18 (B0)
BD0: CN2.75, CN3.75, CN4.75, CN5.75, CN6.75, CN14.3 (R3.1), U4.16 (B2)
BD1: CN2.77, CN3.77, CN4.77, CN5.77, CN6.77, CN14.1 (R1.1), U4.18 (B0)
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
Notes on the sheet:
BD7
BA15
_CFGOUT2
BA21
BA8
BD6
BD12
BFC1
BA16
BA13
BD1
_CFGIN4
AUTOCONFIG
_CFGIN5
BD10
BA18
_CFGIN1
BA5
OTHER BUFFER
SPARE
BA3
BA17
REMOTE SIGNALS
POWER GOOD
Push button
BA9
BA1
BD4
BA7
ZORRO
A2000 video slot
BFC0
BFC2
BA6
RESET
BA22
_CFGOUT3
_CFGIN2
BA23
BD0
